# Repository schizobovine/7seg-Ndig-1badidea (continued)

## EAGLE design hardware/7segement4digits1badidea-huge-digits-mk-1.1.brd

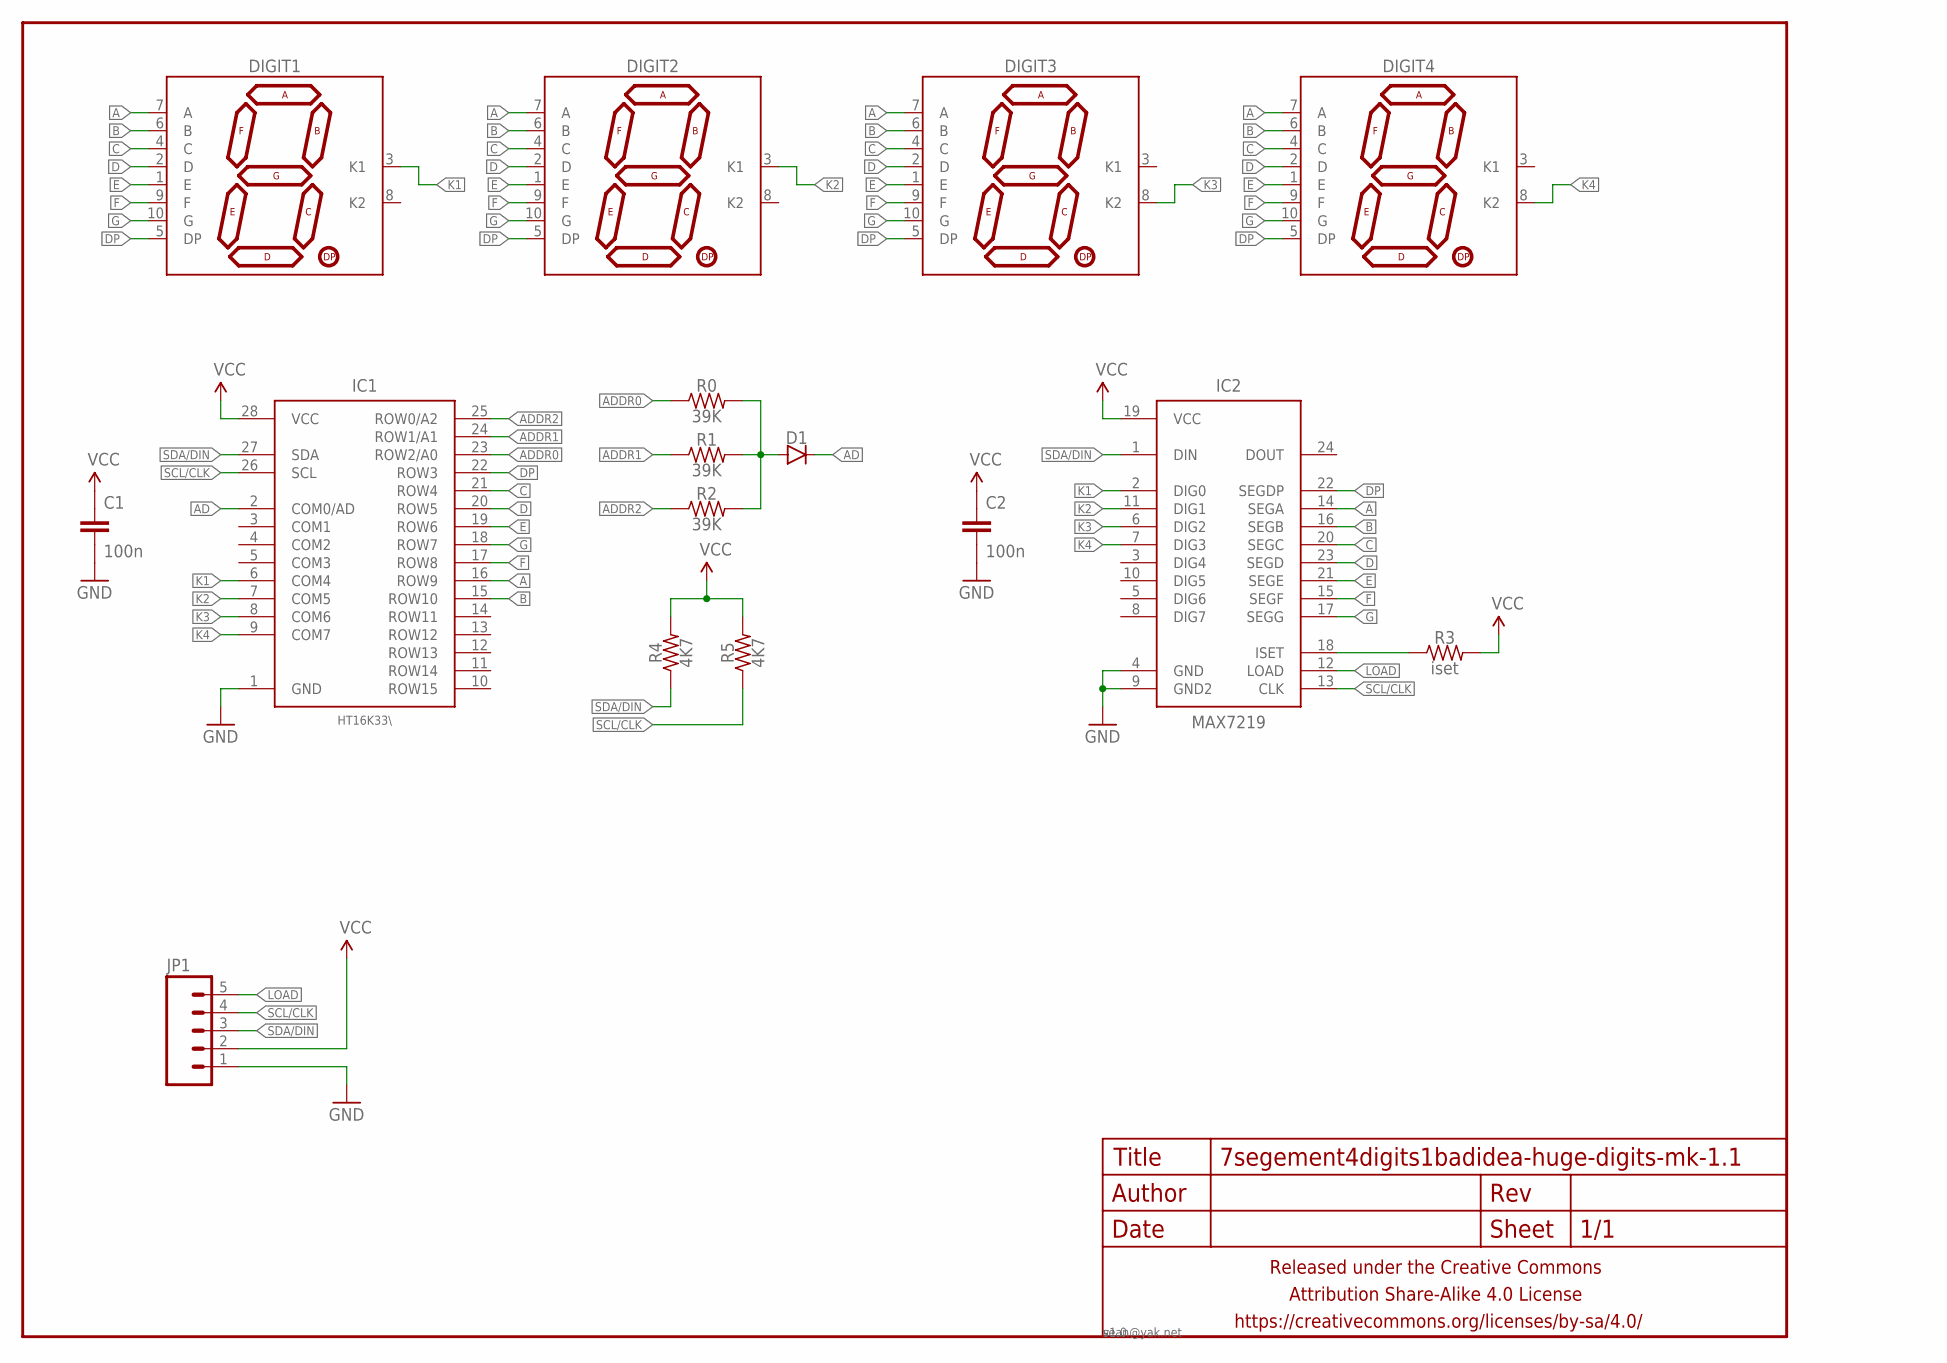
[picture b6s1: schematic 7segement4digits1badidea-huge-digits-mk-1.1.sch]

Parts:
C1, C2: 100n; C0805
D1: DIODESOD123; SOD123
DIGIT1, DIGIT2, DIGIT3, DIGIT4: 7SEG_1DIGPTH-25.4MM; 7SEG_1DIG_25.4MM
FRAME1: FRAME-LETTERNO_PACKAGE; DUMMY
IC1: HT16K33\; SOIC28W
IC2: MAX7219; SO24W
JP1: M05PTH-CENTERED; 1X05_PTH_CENTERED
R0, R1, R2: 39K; R0805
R3: iset; R0805
R4, R5: 4K7; R0805

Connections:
A: DIGIT1.7 (A), DIGIT2.7 (A), DIGIT3.7 (A), DIGIT4.7 (A), IC1.16 (ROW9), IC2.14 (SEGA)
AD: D1.C, IC1.2 (COM0/AD)
ADDR0: IC1.23 (ROW2/A0), R0.1
ADDR1: IC1.24 (ROW1/A1), R1.1
ADDR2: IC1.25 (ROW0/A2), R2.1
B: DIGIT1.6 (B), DIGIT2.6 (B), DIGIT3.6 (B), DIGIT4.6 (B), IC1.15 (ROW10), IC2.16 (SEGB)
C: DIGIT1.4 (C), DIGIT2.4 (C), DIGIT3.4 (C), DIGIT4.4 (C), IC1.21 (ROW4), IC2.20 (SEGC)
D: DIGIT1.2 (D), DIGIT2.2 (D), DIGIT3.2 (D), DIGIT4.2 (D), IC1.20 (ROW5), IC2.23 (SEGD)
DP: DIGIT1.5 (DP), DIGIT2.5 (DP), DIGIT3.5 (DP), DIGIT4.5 (DP), IC1.22 (ROW3), IC2.22 (SEGDP)
E: DIGIT1.1 (E), DIGIT2.1 (E), DIGIT3.1 (E), DIGIT4.1 (E), IC1.19 (ROW6), IC2.21 (SEGE)
F: DIGIT1.9 (F), DIGIT2.9 (F), DIGIT3.9 (F), DIGIT4.9 (F), IC1.17 (ROW8), IC2.15 (SEGF)
G: DIGIT1.10 (G), DIGIT2.10 (G), DIGIT3.10 (G), DIGIT4.10 (G), IC1.18 (ROW7), IC2.17 (SEGG)
GND: C1.2, C2.2, IC1.1 (GND), IC2.4 (GND), IC2.9 (GND2), JP1.1
K1: DIGIT1.3 (K1), IC1.6 (COM4), IC2.2 (DIG0)
K2: DIGIT2.3 (K1), IC1.7 (COM5), IC2.11 (DIG1)
K3: DIGIT3.8 (K2), IC1.8 (COM6), IC2.6 (DIG2)
K4: DIGIT4.8 (K2), IC1.9 (COM7), IC2.7 (DIG3)
LOAD: IC2.12 (LOAD), JP1.5
unnamed: IC2.18 (ISET), R3.1
unnamed: D1.A, R0.2, R1.2, R2.2
SCL/CLK: IC1.26 (SCL), IC2.13 (CLK), JP1.4, R5.1
SDA/DIN: IC1.27 (SDA), IC2.1 (DIN), JP1.3, R4.1
VCC: C1.1, C2.1, IC1.28 (VCC), IC2.19 (VCC), JP1.2, R3.2, R4.2, R5.2

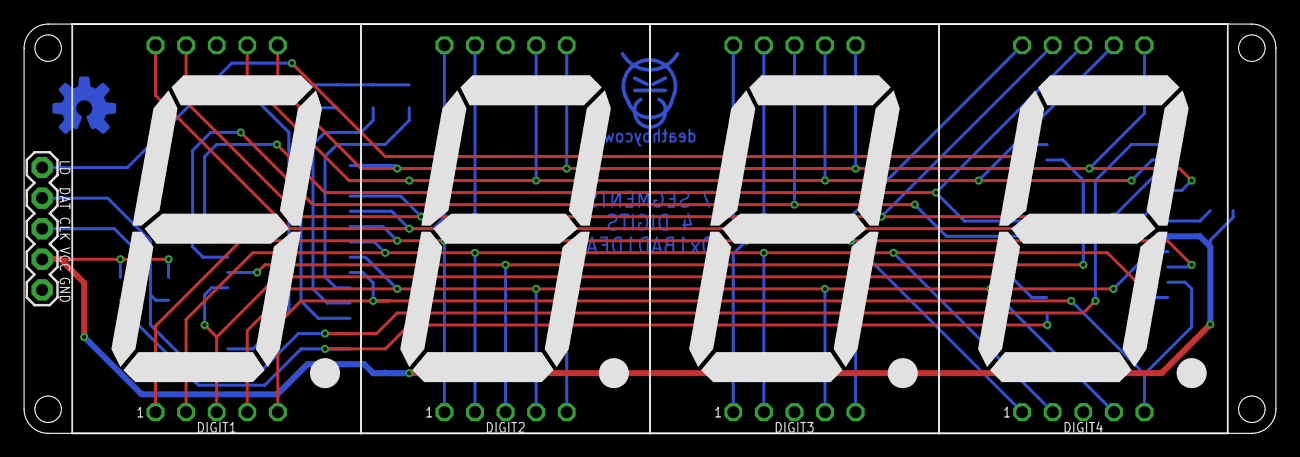
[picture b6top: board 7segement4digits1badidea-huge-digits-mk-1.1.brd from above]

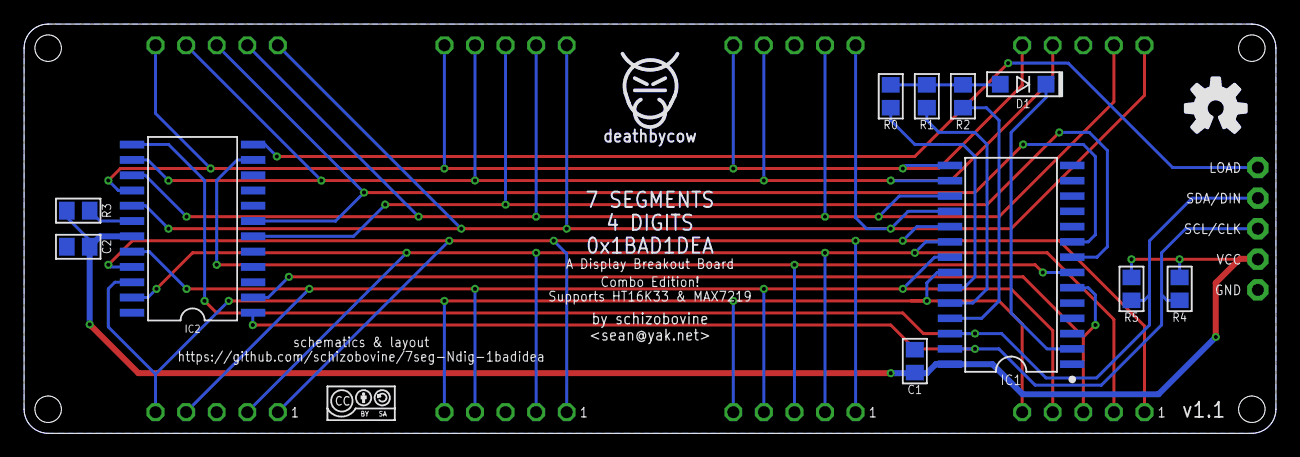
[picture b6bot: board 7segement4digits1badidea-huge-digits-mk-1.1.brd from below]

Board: 2 copper layers, 104.0 x 34.0 mm, 20 parts (14 on the bottom side), 23 nets.

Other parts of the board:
U$1: CC-BY-SA-4.0-NO-URL
U$2: COW_SMALL_METAL
U$3: OSHWLOGO_TOP_0.2_A

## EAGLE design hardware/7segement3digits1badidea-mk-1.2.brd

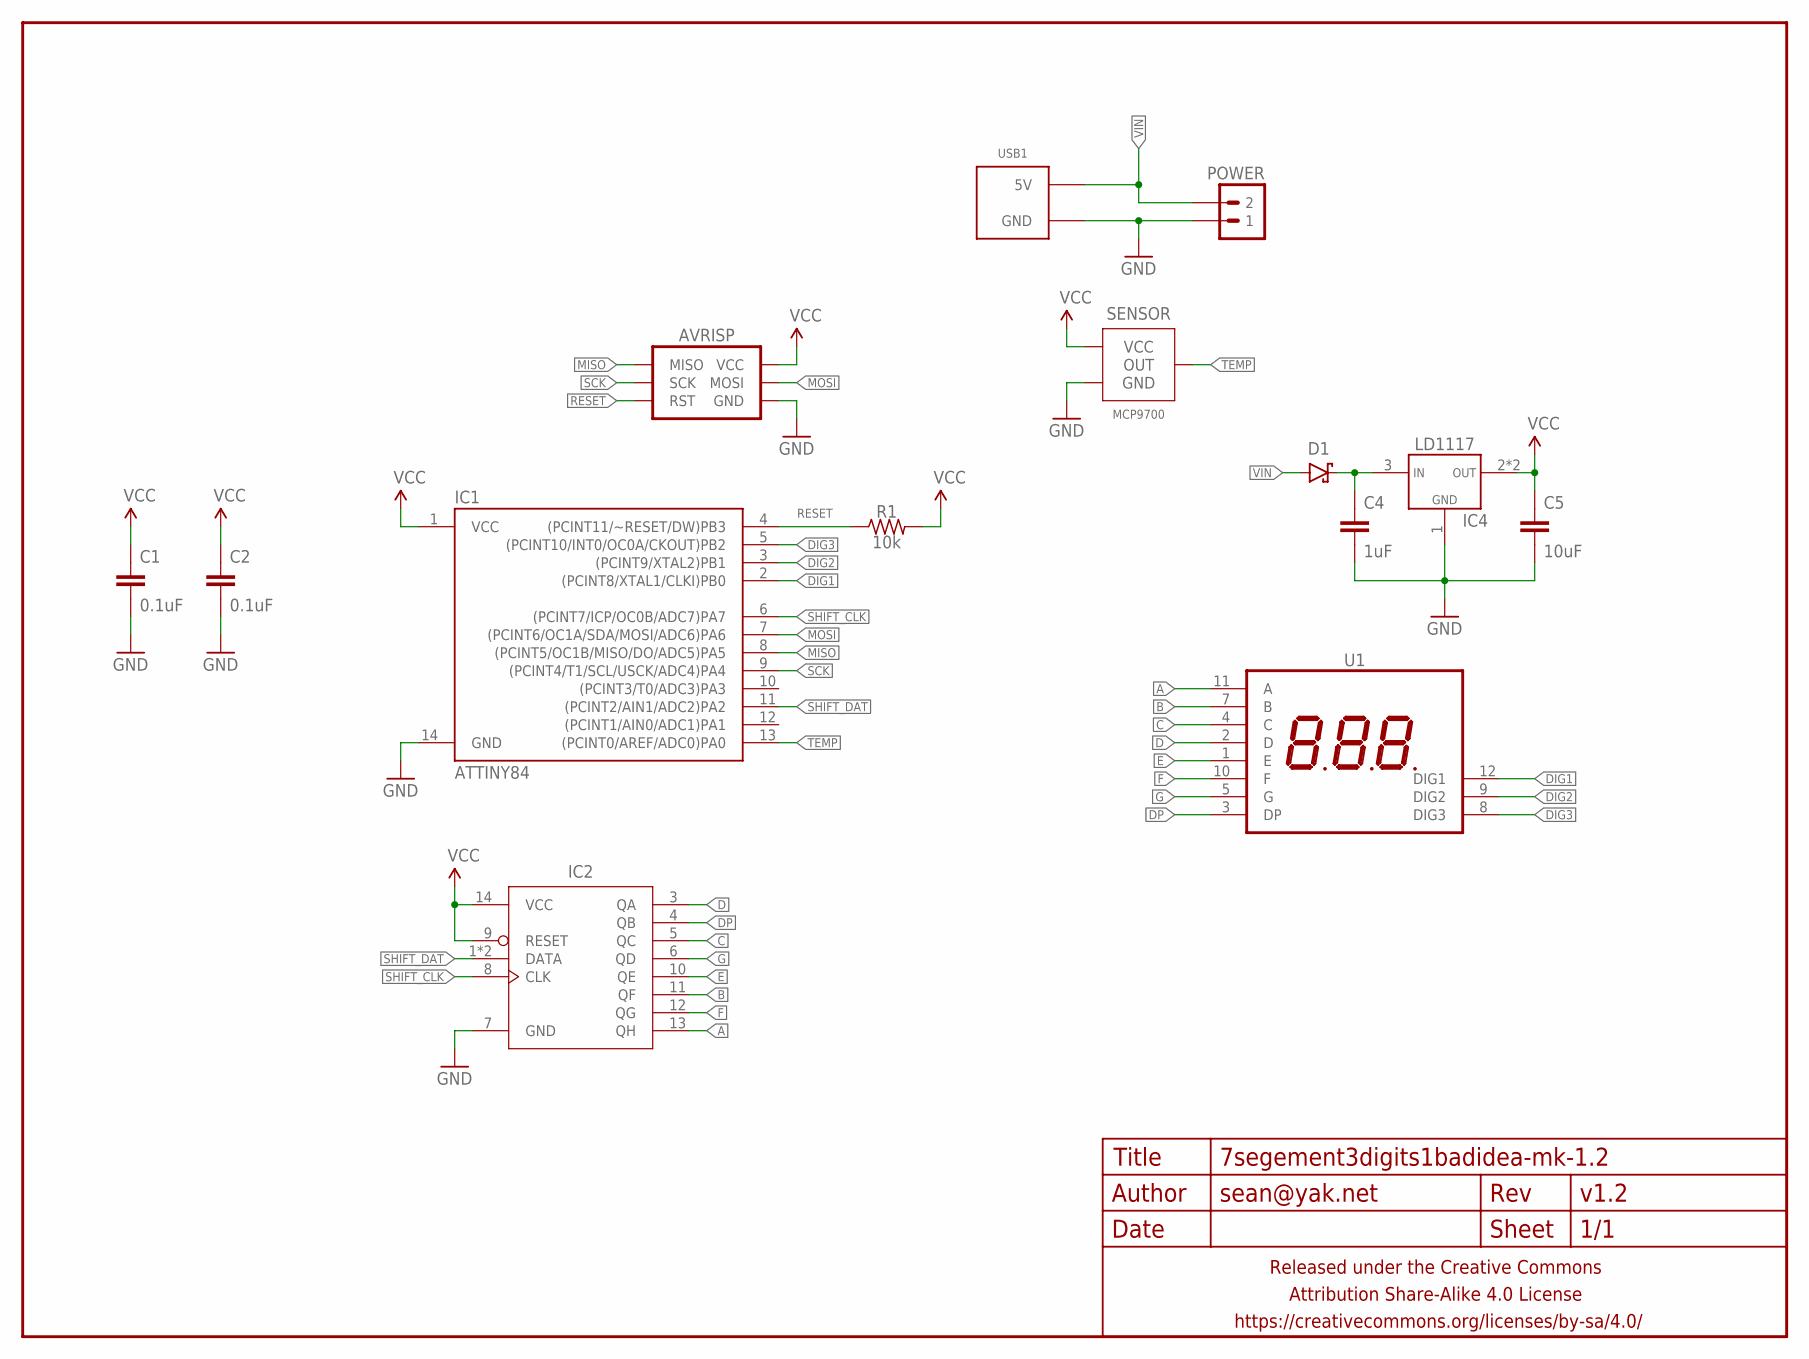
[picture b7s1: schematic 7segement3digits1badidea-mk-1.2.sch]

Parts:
AVRISP: AVR_SPI_PRG_6TESTPOINTS; 2X3_TEST_POINTS
C1, C2: 0.1uF; C0603
C4: 1uF; C0805
C5: 10uF; C0805
D1: DIODE-SCHOTTKYSOD123; SOD123-SCHOTTKY
FRAME1: FRAME-LETTERNO_PACKAGE; DUMMY
IC1: ATTINY84; SO14
IC2: 74HC164; SO14
IC4: LD1117; SOT223
POWER: M02PTH-CENTERED-R+; 1X02-CENTER-R+
R1: 10k; R0603
SENSOR: MCP9700; TO-92-AMMO
U1: 7SEG_3DIGIT; 7SEG_3DIG_0.56IN
USB1: USB_AB_PWRONLY; FCI-10103594-USB-MICRO-B-PWRONLY

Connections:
A: IC2.13 (QH), U1.11 (A)
B: IC2.11 (QF), U1.7 (B)
C: IC2.5 (QC), U1.4 (C)
D: IC2.3 (QA), U1.2 (D)
DIG1: IC1.2 ((PCINT8/XTAL1/CLKI)PB0), U1.12 (DIG1)
DIG2: IC1.3 ((PCINT9/XTAL2)PB1), U1.9 (DIG2)
DIG3: IC1.5 ((PCINT10/INT0/OC0A/CKOUT)PB2), U1.8 (DIG3)
DP: IC2.4 (QB), U1.3 (DP)
E: IC2.10 (QE), U1.1 (E)
F: IC2.12 (QG), U1.10 (F)
G: IC2.6 (QD), U1.5 (G)
GND: AVRISP.6 (GND), C1.2, C2.2, C4.2, C5.2, IC1.14 (GND), IC2.7 (GND), IC4.1 (GND), POWER.1, SENSOR.3 (GND), USB1.5 (GND), USB1.SHIELD@1 (GND), USB1.SHIELD@2 (GND), USB1.SHIELD@3 (GND), USB1.SHIELD@4 (GND)
MISO: AVRISP.1 (MISO), IC1.8 ((PCINT5/OC1B/MISO/DO/ADC5)PA5)
MOSI: AVRISP.4 (MOSI), IC1.7 ((PCINT6/OC1A/SDA/MOSI/ADC6)PA6)
unnamed: C4.1, D1.C, IC4.3 (VIN)
RESET: AVRISP.5 (RST), IC1.4 ((PCINT11/~RESET/DW)PB3), R1.1
SCK: AVRISP.3 (SCK), IC1.9 ((PCINT4/T1/SCL/USCK/ADC4)PA4)
SHIFT_CLK: IC1.6 ((PCINT7/ICP/OC0B/ADC7)PA7), IC2.8 (CLK)
SHIFT_DAT: IC1.11 ((PCINT2/AIN1/ADC2)PA2), IC2.1 (DATA), IC2.2 (DATA)
TEMP: IC1.13 ((PCINT0/AREF/ADC0)PA0), SENSOR.2 (OUT)
VCC: AVRISP.2 (VCC), C1.1, C2.1, C5.1, IC1.1 (VCC), IC2.9 (RESET), IC2.14 (VCC), IC4.2 (VOUT), IC4.4 (VOUT), R1.2, SENSOR.1 (VCC)
VIN: D1.A, POWER.2, USB1.1 (5V)

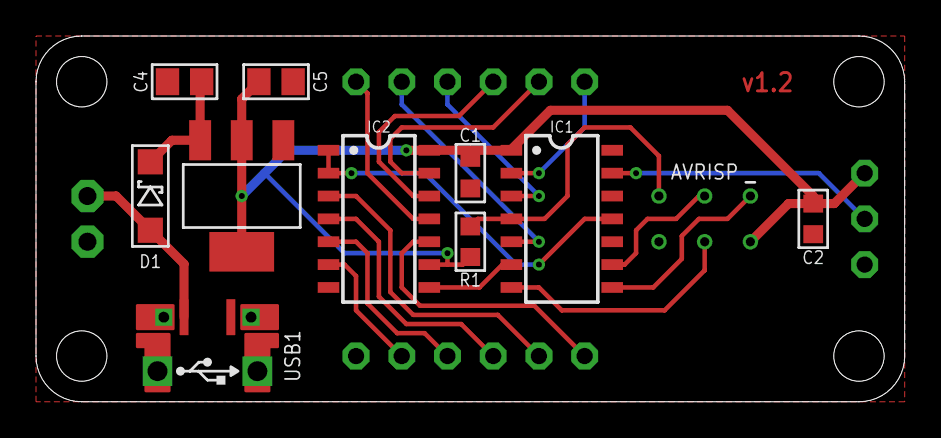
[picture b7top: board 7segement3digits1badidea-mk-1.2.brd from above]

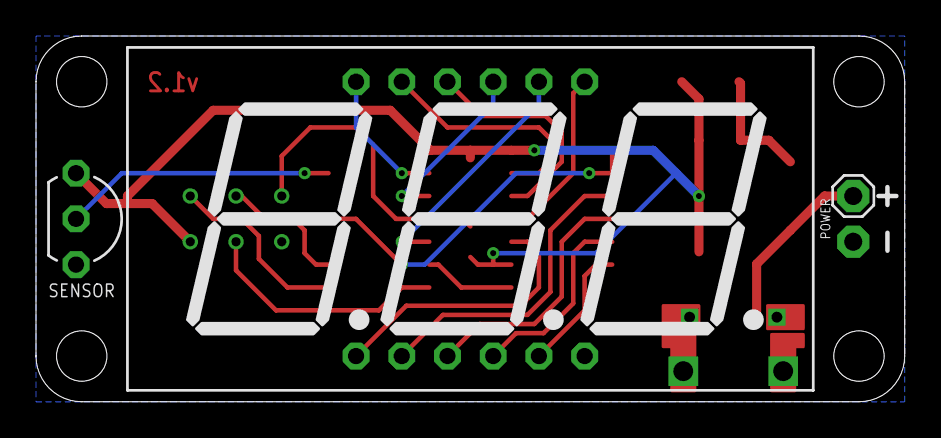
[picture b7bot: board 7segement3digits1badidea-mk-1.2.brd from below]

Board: 2 copper layers, 48.3 x 20.3 mm, 15 parts (3 on the bottom side), 22 nets.

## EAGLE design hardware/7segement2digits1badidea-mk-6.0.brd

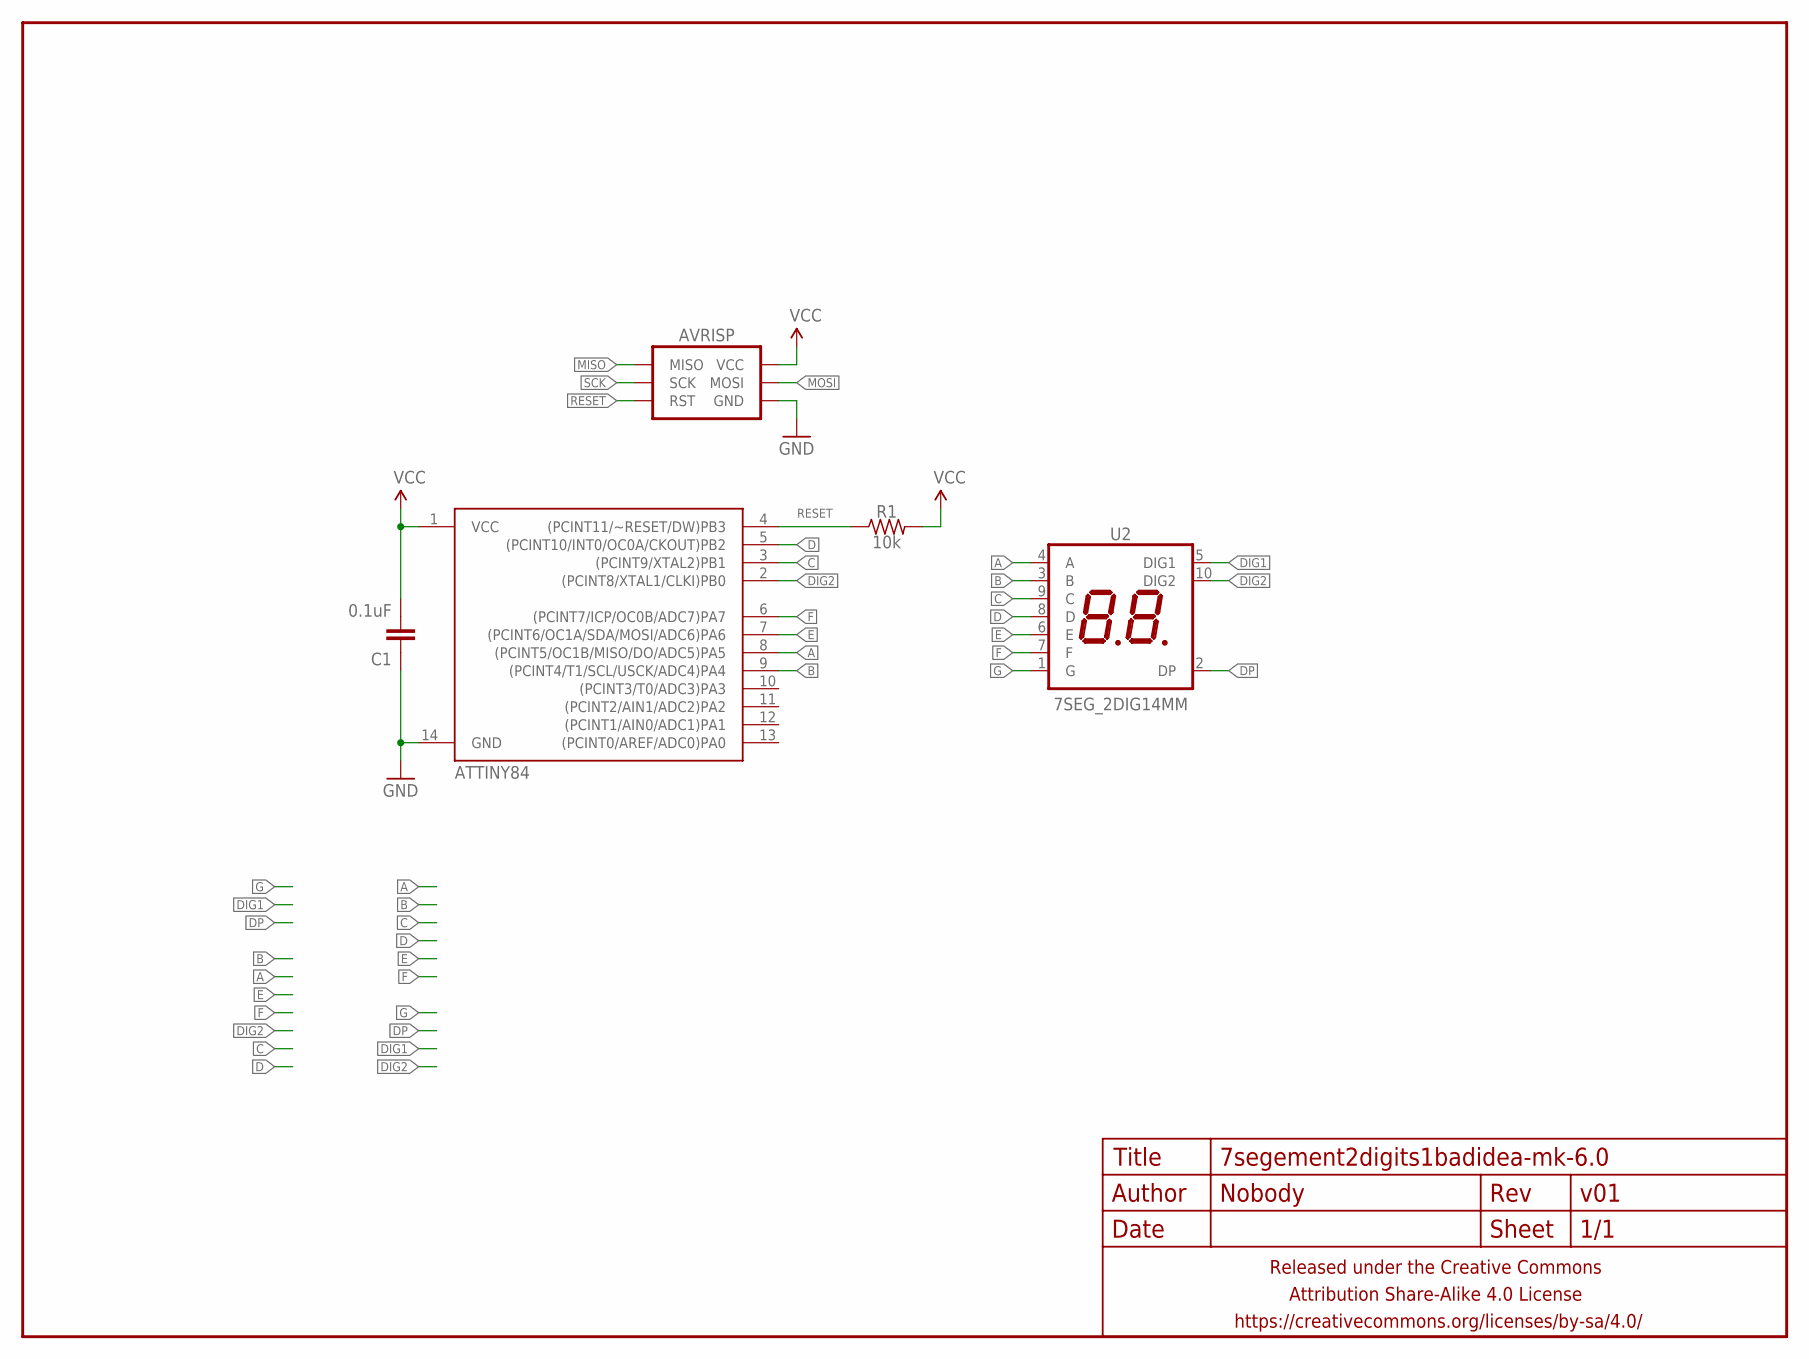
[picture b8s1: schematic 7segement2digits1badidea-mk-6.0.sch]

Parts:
AVRISP: AVR_SPI_PRG_62X3_SMD; 2X3_SMD
C1: 0.1uF; C0603
FRAME1: FRAME-LETTERNO_PACKAGE; DUMMY
R1: 10k; R0603
U1: ATTINY84; SO14
U2: 7SEG_2DIG14MM; 7SEG_2DIG_14MM

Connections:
A: U1.8 ((PCINT5/OC1B/MISO/DO/ADC5)PA5), U2.4 (A)
B: U1.9 ((PCINT4/T1/SCL/USCK/ADC4)PA4), U2.3 (B)
C: U1.3 ((PCINT9/XTAL2)PB1), U2.9 (C)
D: U1.5 ((PCINT10/INT0/OC0A/CKOUT)PB2), U2.8 (D)
DIG1: U2.5 (DIG1)
DIG2: U1.2 ((PCINT8/XTAL1/CLKI)PB0), U2.10 (DIG2)
DP: U2.2 (DP)
E: U1.7 ((PCINT6/OC1A/SDA/MOSI/ADC6)PA6), U2.6 (E)
F: U1.6 ((PCINT7/ICP/OC0B/ADC7)PA7), U2.7 (F)
G: U2.1 (G)
GND: AVRISP.6 (GND), C1.1, U1.14 (GND)
MISO: AVRISP.1 (MISO)
MOSI: AVRISP.4 (MOSI)
RESET: AVRISP.5 (RST), R1.1, U1.4 ((PCINT11/~RESET/DW)PB3)
SCK: AVRISP.3 (SCK)
VCC: AVRISP.2 (VCC), C1.2, R1.2, U1.1 (VCC)

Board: 2 copper layers, 6 parts (1 on the bottom side), 10 nets, no tracks yet.

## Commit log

2014-12-30 initial checkin
2014-12-30 added description
2015-01-09 ADD ALL THE VERSIONS
2015-02-13 hoping this will work if i bend the legs of the display
2015-02-14 fiddlin'
2015-04-08 lots of terribad ideas here
2015-05-11 updating with most recent work?
2015-06-16 gonna use these suckers somehow
2015-06-22 MORE SMT FOR THE SMT THRONE
2015-06-25 more dicking about
2015-06-26 butts butts
2015-06-27 twaddle
2015-06-27 twaddle2
2015-06-29 wonderboard take me away from here
2015-08-10 double the display double the fun. or something.
2015-08-10 no clue why this is in here but committing anyway. shipit!
2016-03-15 whooooole bunch of designs i apparently never committed
